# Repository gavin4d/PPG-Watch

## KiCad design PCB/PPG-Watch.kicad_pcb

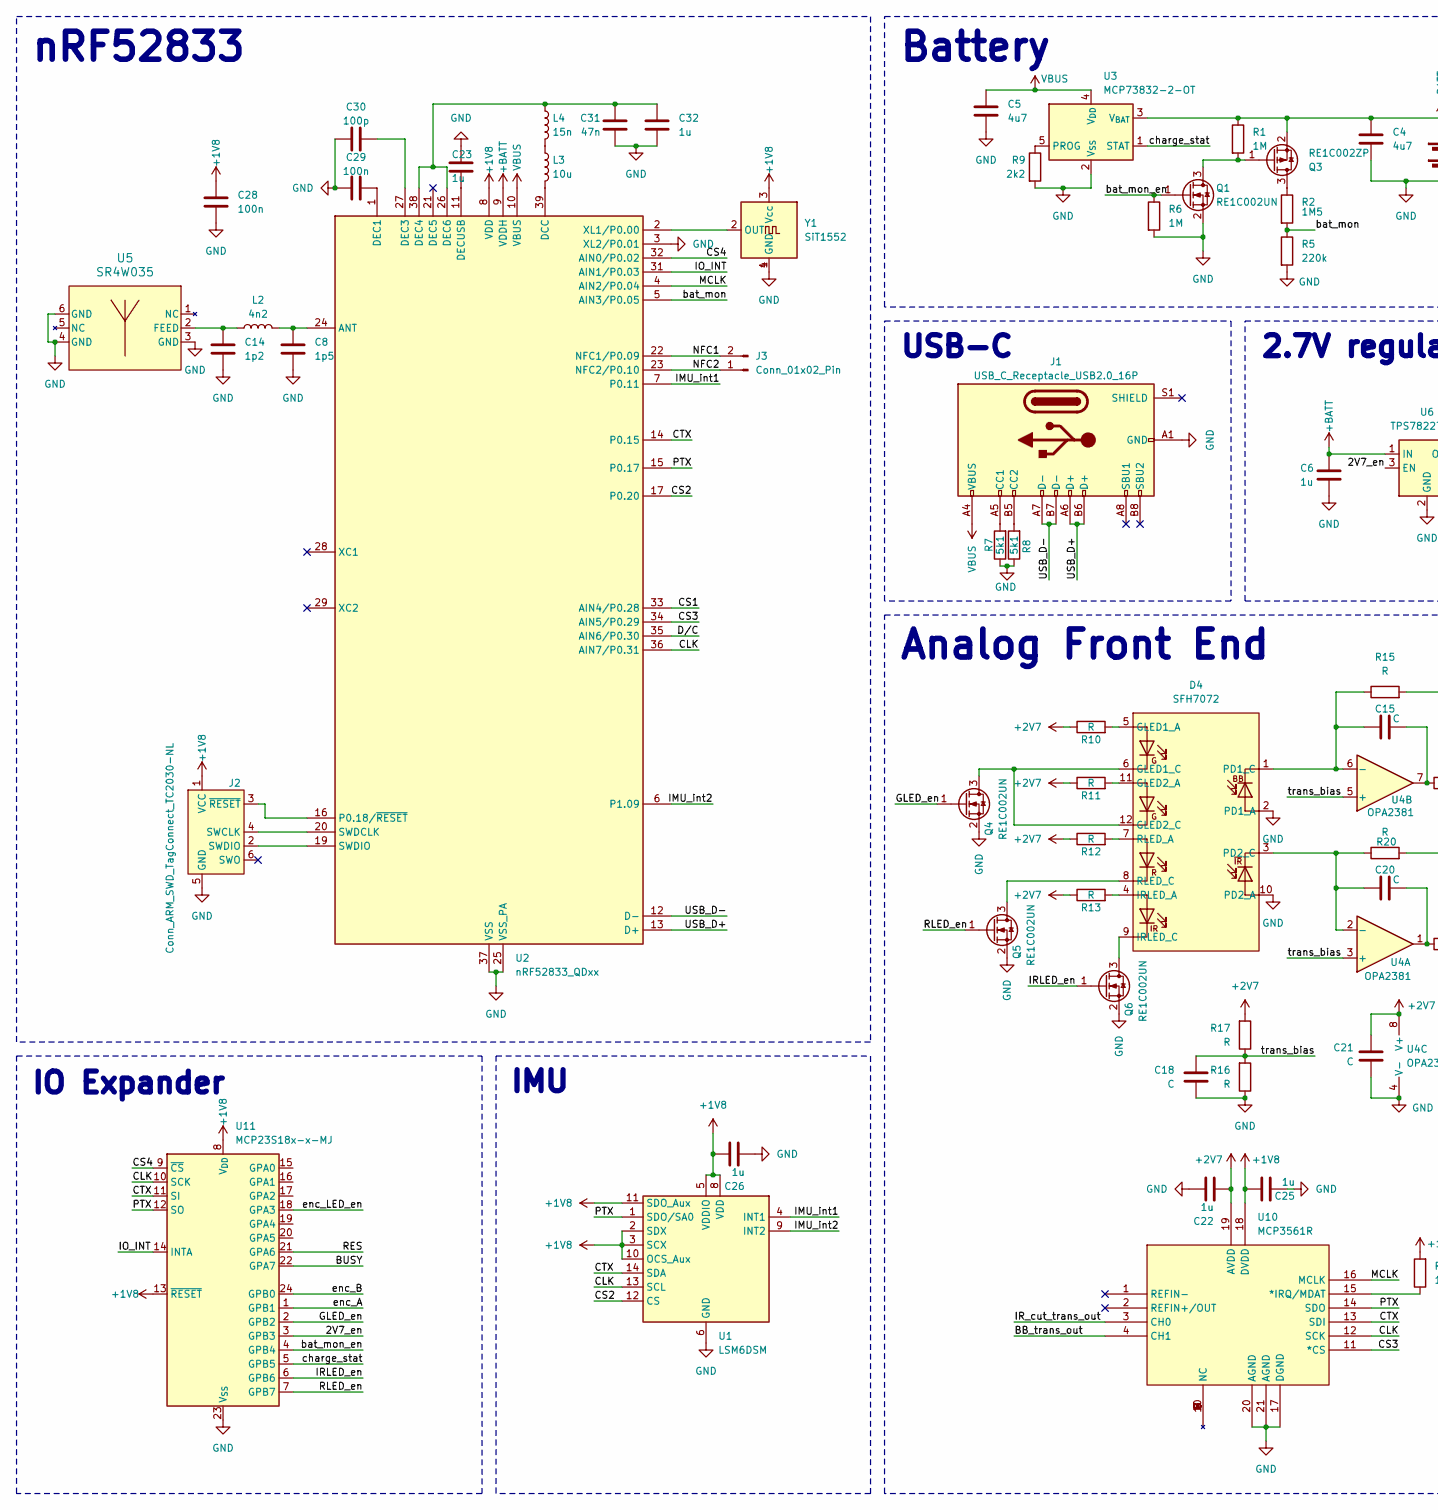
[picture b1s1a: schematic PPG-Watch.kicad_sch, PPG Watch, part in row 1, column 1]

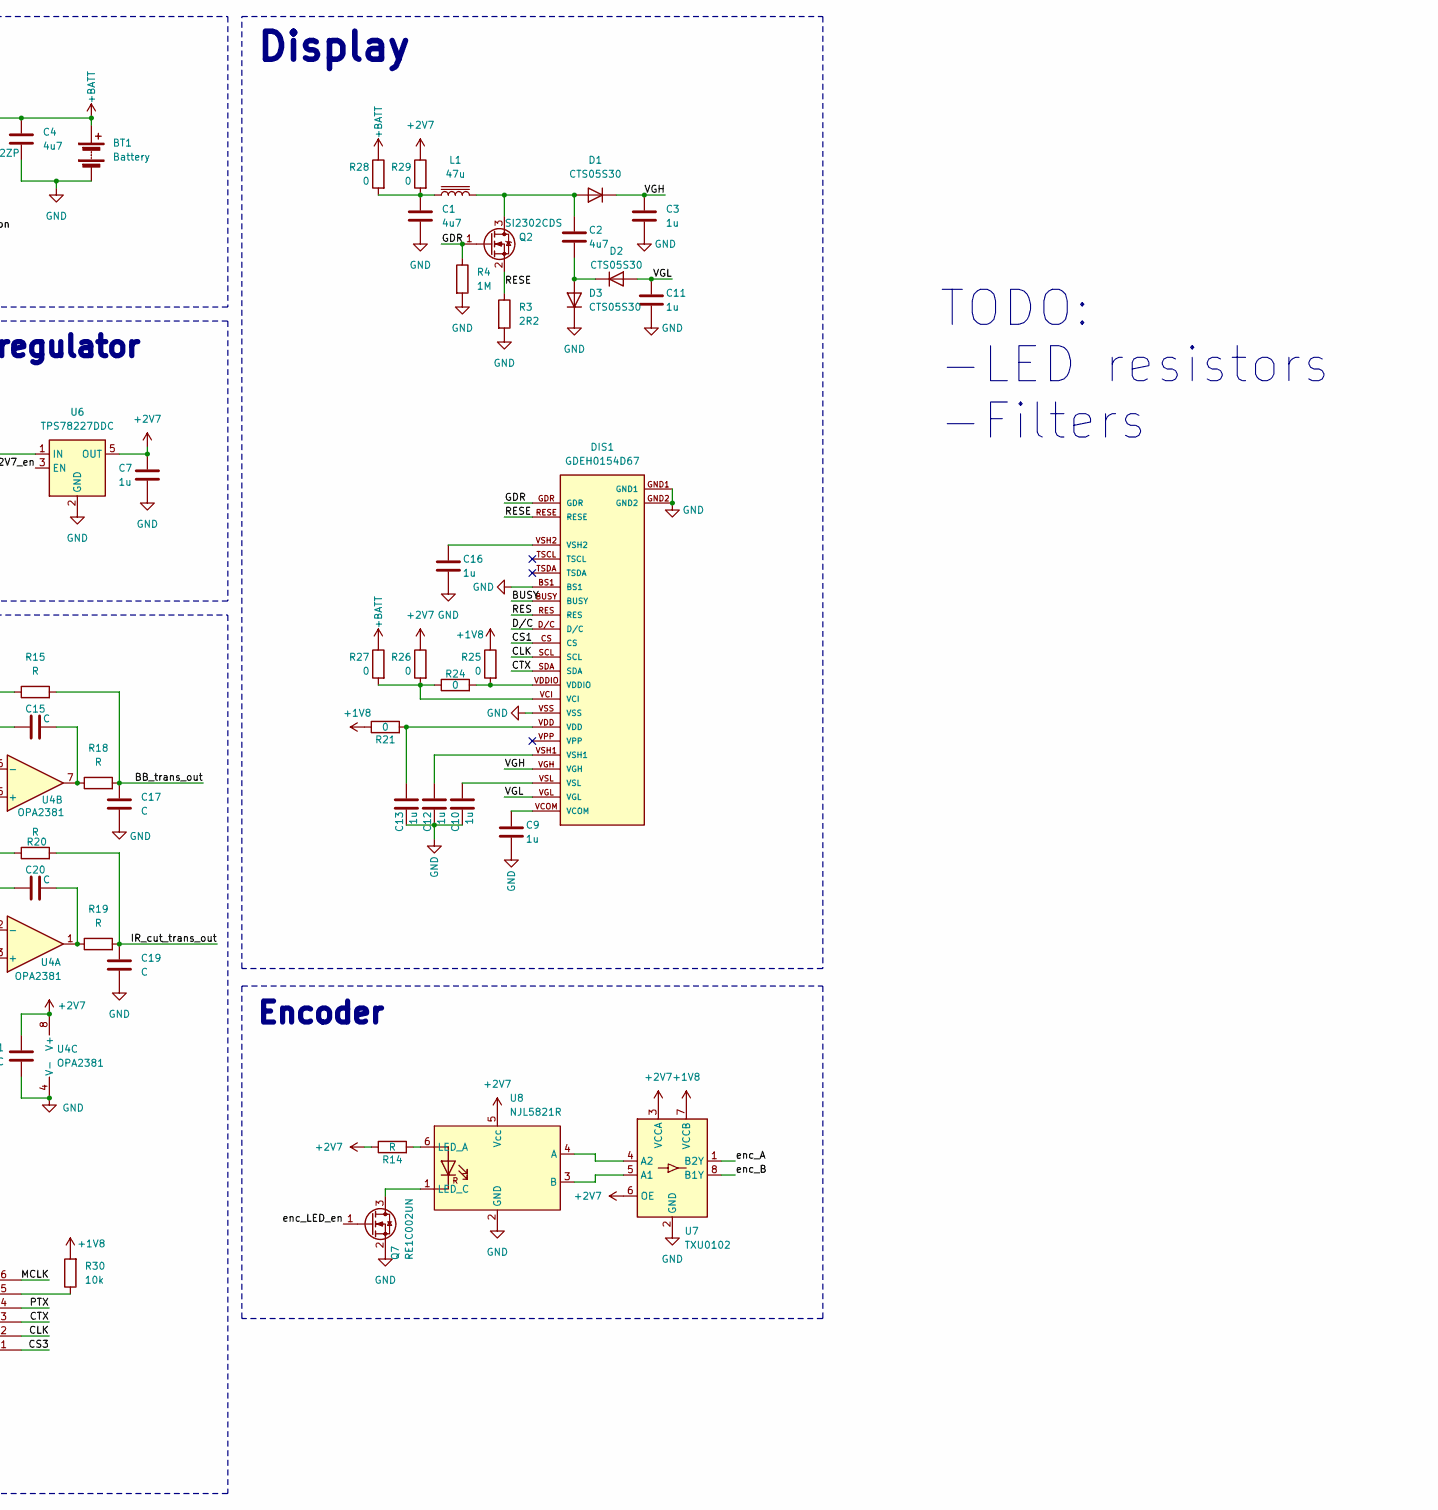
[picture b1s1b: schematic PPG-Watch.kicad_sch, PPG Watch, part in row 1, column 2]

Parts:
BT1: Battery
C1, C2, C4, C5: 4u7; C_0603_1608Metric
C3, C11: 1u; C_0603_1608Metric
C6, C7, C9, C10, C12, C13, C16, C22, C23, C25, C26, C32: 1u; C_0402_1005Metric
C8: 1p5; C_0402_1005Metric
C14: 1p2; C_0402_1005Metric
C15, C17, C18, C19, C20, C21: C; C_0402_1005Metric
C28, C29: 100n; C_0402_1005Metric
C30: 100p; C_0402_1005Metric
C31: 47n; C_0402_1005Metric
D1, D2, D3: CTS05S30; D_SOD-882
D4: SFH7072
DIS1: GDEH0154D67
J1: USB_C_Receptacle_USB2.0_16P; GCT_USB4720-03-A_REVA
J2: Conn_ARM_SWD_TagConnect_TC2030-NL; Tag-Connect_TC2030-IDC-NL_2x03_P1.27mm_Vertical
J3: Conn_01x02_Pin; PinSocket_1x02_P1.00mm_Vertical
L1: 47u; L_Bourns-SRN4018
L2: 4n2; L_0402_1005Metric
L3: 10u; L_0603_1608Metric
L4: 15n; L_0402_1005Metric
Q1, Q4, Q5, Q6, Q7: RE1C002UN; SOT-416
Q2: SI2302CDS; SOT-23
Q3: RE1C002ZP; SOT-416
R1, R4, R6: 1M; R_0402_1005Metric
R2: 1M5; R_0402_1005Metric
R3: 2R2; R_0402_1005Metric
R5: 220k; R_0402_1005Metric
R7, R8: 5k1; R_0402_1005Metric
R9: 2k2; R_0402_1005Metric
R10, R11, R12, R13, R14, R15, R16, R17, R18, R19, R20: R; R_0402_1005Metric
R21, R24, R25, R26, R27, R28, R29: 0; R_0402_1005Metric
R30: 10k; R_0402_1005Metric
U1: LSM6DSM; LGA-14_3x2.5mm_P0.5mm_LayoutBorder3x4y
U2: nRF52833_QDxx; QFN-40-1EP_5x5mm_P0.4mm_EP3.6x3.6mm
U3: MCP73832-2-OT; SOT-23-5
U4: OPA2381; DFN-8-1EP_3x3mm_P0.65mm_EP1.55x2.4mm
U5: SR4W035; SR4W035_4X6_ANT
U6: TPS78227DDC; SOT-23-5
U7: TXU0102; X1SON-8_1.05x2mm_P0.5mm
U8: NJL5821R
U10: MCP3561R; QFN-20-1EP_3x3mm_P0.4mm_EP1.65x1.65mm
U11: MCP23S18x-x-MJ; HVQFN-24-1EP_4x4mm_P0.5mm_EP2.6x2.6mm_ThermalVias
Y1: SiT1552

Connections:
+1V8: C25.1, C26.1, C28.1, J2.1 (VCC), R21.1, R25.1, R30.2, U1.2 (SDX), U1.3 (SCX), U1.5 (VDDIO), U1.8 (VDD), U1.10 (OCS_Aux), U1.11 (SDO_Aux), U2.8 (VDD), U2.18 (VDD), U2.30 (VDD), U2.40 (VDD), U7.7 (VCCB), U10.18 (DVDD), U11.8 (V_{DD}), U11.13 (~RESET), Y1.3 (Vcc)
+2V7: C7.1, C21.1, C22.2, R10.1, R11.1, R12.1, R13.1, R14.1, R17.2, R26.1, R29.1, U4.8 (V+), U6.5 (OUT), U7.3 (VCCA), U7.6 (OE), U8.5 (Vcc), U10.19 (AVDD)
+BATT: BT1.1 (+), C4.1, C6.1, Q3.2 (S), R1.1, R27.1, R28.1, U2.9 (VDDH), U3.3 (V_{BAT}), U6.1 (IN)
/2V7_en: U6.3 (EN), U11.3 (GPB3)
/BB_trans_out: C17.1, R15.2, R18.2, U10.4 (CH1)
/BUSY: DIS1.BUSY, U11.22 (GPA7)
/CLK: DIS1.SCL, U1.13 (SCL), U2.36 (AIN7/P0.31), U10.12 (SCK), U11.10 (SCK)
/CS1: DIS1.CS, U2.33 (AIN4/P0.28)
/CS2: U1.12 (CS), U2.17 (P0.20)
/CS3: U2.34 (AIN5/P0.29), U10.11 (*CS)
/CS4: U2.32 (AIN0/P0.02), U11.9 (~CS)
/CTX: DIS1.SDA, U1.14 (SDA), U2.14 (P0.15), U10.13 (SDI), U11.11 (SI)
/D/C: DIS1.D/C, U2.35 (AIN6/P0.30)
/GDR: DIS1.GDR, Q2.1 (G), R4.1
/GLED_en: Q4.1 (G), U11.2 (GPB2)
/IMU_int1: U1.4 (INT1), U2.7 (P0.11)
/IMU_int2: U1.9 (INT2), U2.6 (P1.09)
/IO_INT: U2.31 (AIN1/P0.03), U11.14 (INTA)
/IRLED_en: Q6.1 (G), U11.6 (GPB6)
/IR_cut_trans_out: C19.1, R19.2, R20.2, U10.3 (CH0)
/MCLK: U2.4 (AIN2/P0.04), U10.16 (MCLK)
/NFC1: J3.2, U2.22 (NFC1/P0.09)
/NFC2: J3.1, U2.23 (NFC2/P0.10)
/PTX: U1.1 (SDO/SA0), U2.15 (P0.17), U10.14 (SDO), U11.12 (SO)
/RES: DIS1.RES, U11.21 (GPA6)
/RESE: DIS1.RESE, Q2.2 (S), R3.1
/RLED_en: Q5.1 (G), U11.7 (GPB7)
/USB_D+: J1.A6 (D+), J1.B6 (D+), U2.13 (D+)
/USB_D-: J1.A7 (D-), J1.B7 (D-), U2.12 (D-)
/VGH: C3.1, D1.1 (K), DIS1.VGH
/VGL: C11.1, D2.2 (A), DIS1.VGL
/bat_mon: R2.2, R5.1, U2.5 (AIN3/P0.05)
/bat_mon_en: Q1.1 (G), R6.1, U11.4 (GPB4)
/charge_stat: U3.1 (STAT), U11.5 (GPB5)
/enc_A: U7.1 (B2Y), U11.1 (GPB1)
/enc_B: U7.8 (B1Y), U11.24 (GPB0)
/enc_LED_en: Q7.1 (G), U11.18 (GPA3)
/trans_bias: C18.1, R16.2, R17.1, U4.3 (+), U4.5 (+)
GND: BT1.2 (-), C1.2, C3.2, C4.2, C5.2, C6.2, C7.2, C8.2, C9.2, C10.1, C11.2, C12.1, C13.1, C14.2, C16.2, C17.2, C18.2, C19.2, C21.2, C22.1, C23.1, C25.2, C26.2, C28.2, C29.1, C30.1, C31.2, C32.2, D3.1 (K), D4.2 (PD1_A), D4.10 (PD2_A), DIS1.BS1, DIS1.GND1, DIS1.GND2, DIS1.VSS, J1.A1 (GND), J1.A12 (GND), J1.B1 (GND), J1.B12 (GND), J2.5 (GND), Q1.2 (S), Q4.2 (S), Q5.2 (S), Q6.2 (S), Q7.2 (S), R3.2, R4.2, R5.2, R6.2, R7.1, R8.1, R9.2, R16.1, U1.6 (GND), U1.7 (GND), U2.3 (XL2/P0.01), U2.25 (VSS_PA), U2.37 (VSS), U2.41 (VSS), U3.2 (V_{SS}), U4.4 (V-), U4.9, U5.3 (GND), U5.4 (GND), U5.6 (GND), U6.2 (GND), U6.4 (GND), U7.2 (GND), U8.2 (GND), U10.17 (DGND), U10.20 (AGND), U10.21 (AGND), U11.23 (V_{SS}), Y1.1 (GND), Y1.4 (GND)
unnamed: C1.1, L1.1, R28.2, R29.2
unnamed: C9.1, DIS1.VCOM
unnamed: C10.2, DIS1.VSL
unnamed: C12.2, DIS1.VSH1
unnamed: C13.2, DIS1.VDD, R21.2
unnamed: C15.2, R18.1, U4.7
unnamed: C16.1, DIS1.VSH2
unnamed: C20.2, R19.1, U4.1
unnamed: C2.1, D1.2 (A), L1.2, Q2.3 (D)
unnamed: C2.2, D2.1 (K), D3.2 (A)
unnamed: D4.5 (GLED1_A), R10.2
unnamed: D4.6 (GLED1_C), D4.12 (GLED2_C), Q4.3 (D)
unnamed: D4.11 (GLED2_A), R11.2
unnamed: D4.4 (IRLED_A), R13.2
unnamed: D4.9 (IRLED_C), Q6.3 (D)
unnamed: C15.1, D4.1 (PD1_C), R15.1, U4.6 (-)
unnamed: C20.1, D4.3 (PD2_C), R20.1, U4.2 (-)
unnamed: D4.7 (RLED_A), R12.2
unnamed: D4.8 (RLED_C), Q5.3 (D)
unnamed: DIS1.VCI, R24.1, R26.2, R27.2
unnamed: DIS1.VDDIO, R24.2, R25.2
unnamed: J1.A5 (CC1), R7.2
unnamed: J1.B5 (CC2), R8.2
unnamed: J2.4 (SWCLK), U2.20 (SWDCLK)
unnamed: J2.2 (SWDIO), U2.19 (SWDIO)
unnamed: J2.3 (~RESET), U2.16 (P0.18/~RESET)
unnamed: L3.1, L4.2
unnamed: Q1.3 (D), Q3.1 (G), R1.2
unnamed: Q3.3 (D), R2.1
unnamed: Q7.3 (D), U8.1 (LED_C)
unnamed: C8.1, L2.2, U2.24 (ANT)
unnamed: L3.2, U2.39 (DCC)
unnamed: C29.2, U2.1 (DEC1)
unnamed: C30.2, U2.27 (DEC3)
unnamed: C31.1, C32.1, L4.1, U2.26 (DEC6), U2.38 (DEC4)
unnamed: C23.2, U2.11 (DECUSB)
unnamed: U2.2 (XL1/P0.00), Y1.2 (OUT)
unnamed: R9.1, U3.5 (PROG)
unnamed: C14.1, L2.1, U5.2 (FEED)
unnamed: U7.5 (A1), U8.3 (B)
unnamed: U7.4 (A2), U8.4 (A)
unnamed: R14.2, U8.6 (LED_A)
unnamed: R30.1, U10.15 (*IRQ/MDAT)
VBUS: C5.1, J1.A4 (VBUS), J1.A9 (VBUS), J1.B4 (VBUS), J1.B9 (VBUS), U2.10 (VBUS), U3.4 (V_{DD})

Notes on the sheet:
IMU
Analog Front End
IO Expander
Encoder
Battery
Display
TODO: -LED resistors -Filters
2.7V regulator
nRF52833
USB-C

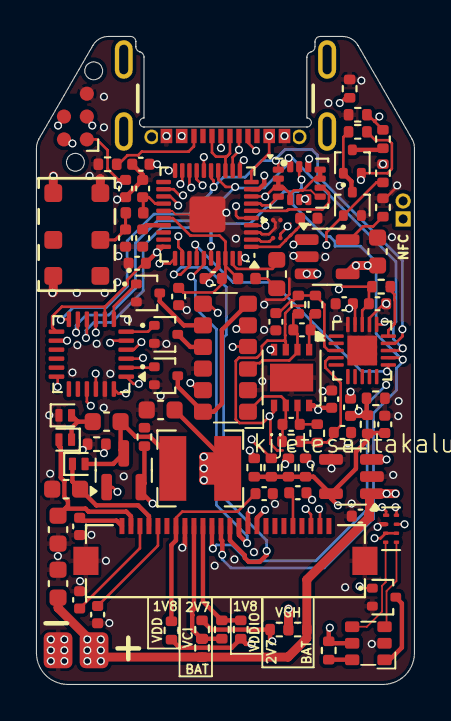
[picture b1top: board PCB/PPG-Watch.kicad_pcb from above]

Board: 6 copper layers, 21.0 x 36.0 mm, 89 parts (0 on the bottom side), 83 nets.

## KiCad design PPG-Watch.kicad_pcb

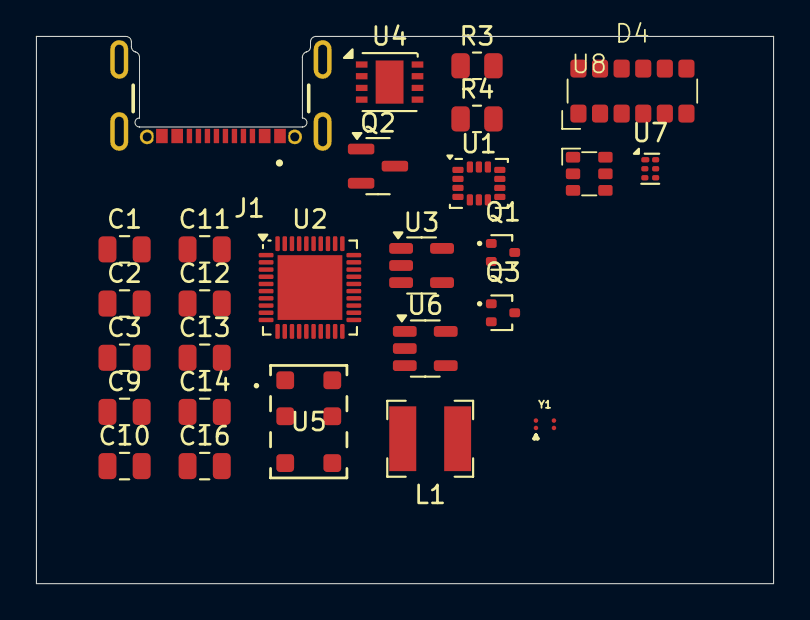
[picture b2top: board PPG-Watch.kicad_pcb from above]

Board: 2 copper layers, 40.9 x 30.4 mm, 27 parts (0 on the bottom side), 10 nets, no tracks yet.

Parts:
C1, C2: 4.7u; C_0805_2012Metric
C3, C9, C10, C11, C12, C13, C14, C16: 1u; C_0805_2012Metric
D4: SFH7072
J1: USB_C_Receptacle_USB2.0_16P; GCT_USB4720-03-A_REVA
L1: 47uH; L_Bourns-SRN4018
Q1: RE1C002UN; SOT-416
Q2: SI2302CDS; SOT-23
Q3: RE1C002ZP; SOT-416
R3: 2.2; R_0805_2012Metric
R4: 1M; R_0805_2012Metric
U1: LSM6DSM; LGA-14_3x2.5mm_P0.5mm_LayoutBorder3x4y
U2: nRF52833_QDxx; QFN-40-1EP_5x5mm_P0.4mm_EP3.6x3.6mm
U3: MCP73832-2-OT; SOT-23-5
U4: OPA2381; DFN-8-1EP_3x3mm_P0.65mm_EP1.55x2.4mm
U5: SR4W035; SR4W035_4X6_ANT
U6: TPS78227DDC; SOT-23-5
U7: TXU0101; Texas_USON-6_1x1.45mm_P0.5mm_SMD
U8: NJL5821R
Y1: SiT1552

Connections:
/GDR: Q2.1 (G), R4.1
/RESE: Q2.2 (S), R3.1
GND: C1.2, C3.2, C9.2, C10.1, C11.2, C12.1, C13.1, C14.1, C16.2, R3.2, R4.2
unnamed: C1.1, L1.1
unnamed: C2.1, L1.2, Q2.3 (D)
unnamed: U1.6 (GND), U1.7 (GND)
unnamed: U2.8 (VDD), U2.18 (VDD), U2.30 (VDD), U2.40 (VDD)
unnamed: U2.37 (VSS), U2.41 (VSS)
unnamed: U6.2 (GND), U6.4 (GND)
unnamed: Y1.1 (GND), Y1.4 (GND)

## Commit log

2025-10-23 renamed library
2025-10-23 added gitignore
2025-10-23 removed backup folder
2025-10-28 Schematic: trans amp ADC IO power
2025-10-28 update gitignore
2025-11-10 inital component placement
2025-11-10 gitignore
2025-11-19 layout complete!!!
2025-11-20 board ordered!!!
